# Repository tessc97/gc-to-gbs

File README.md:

# GCtoGBS
The GCtoGBS board is supposed to provide a cheaper way to connect (mainly Nintendo) consoles to a [gbs-control](https://github.com/ramapcsx2/gbs-control) by using cheap components and VGA/Aux cables.

It provides multiple solder jumpers and optional components to configure your signal output exactly to your needs for any console.

This probably makes the most sense if you have multiple consoles that you want to hook up to your gbs-control. Just order a bunch of PCBs from JLCPCB or any other PCB manufacturer, order the parts and assemble yourself. I designed the board to be able to be hand soldered.

This is my first PCB design project. Feel free to point out any mistakes or improvements I could make. This project is also completely open source.

PS: The original name of this project was gc-to-vga because I planned on doing one board per console. Then I changed it to gc-to-gbs because most modern VESA VGA monitors won't be able to read the RGBS/RGBHV signal this outputs. Last, I decided to make this board configurable by jumpers and optional components so it's one board for every console/mod but stuck with the name.

# Settings
Depending on the console or mod you have, you need to set jumpers and add/leave out components to match the following specs.

## Sync
### Native CSync
If your console outputs native CSync, you have the following options:
* Console outputs TTL CSync:
    * Solder jumper JP4 if you do not have a 100 Ohm resistor to ground on your GBS
    * Add a 470 Ohm resistor to R4 if you have the 100 Ohm resistor on your GBS
* Console outputs 75 Ohm CSync
    * Solder jumper JP4; 100 Ohm resistor to ground on GBS should be present

**Never solder JP4 on a PAL SNES or Gamecube as these have +12V on Pin 3**

### LM1881 Sync
If you want to use the built-in LM1881 for CSync and VSync, you need to first select the signal you want to strip Sync from:
* For Sync on Green solder JP1
* For Sync on Luma solder JP2
* For Sync on Composite solder JP3

Then you need to do one of the following:
* Solder jumper JP5 if you need a TTL signal (no 100 Ohm from Sync to GND on GBS)
* Add a 470 Ohm resistor to R5 if you need a 75 Ohm signal

If you want to add VSync to your VGA cable, do one of the following:
* Solder jumper JP6
* Add 470 Ohm resistor to R6

I'm not entirely sure yet which of these is better for the GBS, but since most people only solder a 100 Ohm resistor to ground on the pin that is connected to CSync/HSync, the GBS probably expects a TTL signal (if any at all), so it's probably best to just solder the jumper closed.

If you don't need VSync and your console has built in CSync, you can leave out the LM1881.

## RGB signal
### 75 Ohm termination
Some consoles are already 75 Ohm terminated (PAL Gamecube, NESRGB) but some need a 75 Ohm resistor to ground on each of the RGB color lines.

Solder a 75 Ohm resistor to R3, R7 and R8 if you console needs the 75 Ohm termination, i.e. the PAL SNES.

### Brightness
If you need to control the brigthness of your RGB signal, you can add three capacitors to C3, C4 and C5. According to [this](https://gamesx.com/wiki/doku.php?id=av:nintendomultiav), the PAL Gamecube needs a 220uF cap on every RGB line but the PAL SNES does not due to a different RGB circuit.

Some other documentations and threads also mention 470uF caps. I have not read into the whole thing but you might want to try different values here.

## Example settings
### PAL Gamecube (100R on GBS Sync to GND)
Soldered jumpers:
* JP3 for Sync on Composite
* JP6 for TTL level VSync (or no VSync at all)

Components:
* 470 Ohm resistor on R5
* 220uF capacitors on C4, C5 and C6

### NESRGB configured for TTL (no 100R on GBS Sync to GND)
Soldered jumpers:
* JP4 for TTL level CSync from MultiAV Pin 3
* JP7, JP8 and JP9 because NESRGB has built-in 220uF caps

### PAL SNES (100R on GBS Sync to GND)
Soldered jumpers:
* JP2 for Sync on Luma
* JP7, JP8 and JP9 to bypass the capacitors

Components:
* 470 Ohm resistor on R5
* 75 Ohm resistors on R3, R7 and R8 for 75 Ohm Termination

# Required components
These are "optional" if your console already has CSync and you don't need VSync.
* 100nF capacitors on C1, C2 and C3
* 75 Ohm resistor on R1
* 680k resistor on R2

# Connectors
I spec'd this for the following connectors:
* 12 pin JST-XH header
    * plus MultiAV to 12 pin JST connector
* D-Sub 15 HD female horizontal socket for VGA
* SJ1-3533NG horizontal 3.5mm audio jack socket

You can also just solder the conductors to the board. I will probably not bother with the 12-pin JST connector and header myself as those are kind of expensive.
I ordered some MutliAV plugs from Aliexpress to make a full-on adapter.

# Case
I am currently designing a 3D-printable case for this board. I will update the repository once I finished and tested it.

# ToDos
* Update Readme with images
* Design 3D-printable case
* Assemble prototye and test

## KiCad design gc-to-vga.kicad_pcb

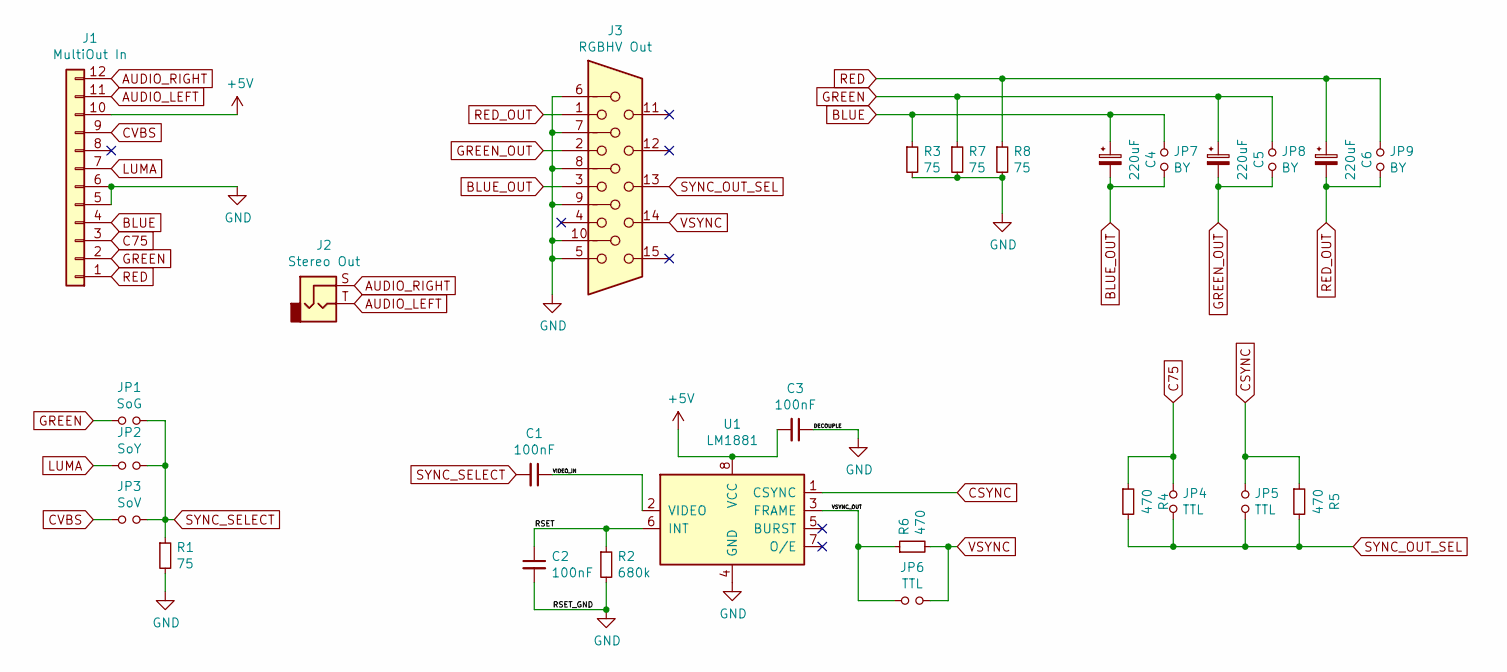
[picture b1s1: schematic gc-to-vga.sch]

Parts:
C1, C3: 100nF; C_0805_2012Metric; Part CL21B104KBCNFNC‎
C2: 100nF; C_0805_2012Metric
C4, C5, C6: 220uF; CP_Radial_D8.0mm_P3.80mm; Part UWX1A221MCL1GB‎
J1: MultiOut In; JST_XH_B12B-XH-A_1x12_P2.50mm_Vertical; Part B12B-XH-A
J2: Stereo Out; Jack_3.5mm_CUI_SJ1-3533NG_Horizontal; Part ‎SJ1-3533N‎
J3: RGBHV Out; DSUB-15-HD_Female_Horizontal_P2.29x1.98mm_EdgePinOffset3.03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; Part L717HDE15PD4CH4R‎
JP1: SoG; SolderJumper-2_P1.3mm_Open_TrianglePad1.0x1.5mm
JP2: SoY; SolderJumper-2_P1.3mm_Open_TrianglePad1.0x1.5mm
JP3: SoV; SolderJumper-2_P1.3mm_Open_TrianglePad1.0x1.5mm
JP4, JP5, JP6: TTL; SolderJumper-2_P1.3mm_Open_TrianglePad1.0x1.5mm
JP7, JP8, JP9: BY; SolderJumper-2_P1.3mm_Open_TrianglePad1.0x1.5mm
R1: 75; R_1206_3216Metric_Pad1.30x1.75mm_HandSolder; Part RK73H2BTTD75R0F‎
R2: 680k; R_1206_3216Metric_Pad1.30x1.75mm_HandSolder
R3, R7, R8: 75; R_1206_3216Metric_Pad1.30x1.75mm_HandSolder
R4, R5: 470; R_1206_3216Metric_Pad1.30x1.75mm_HandSolder; Part CRG1206F470R‎
R6: 470; R_1206_3216Metric_Pad1.30x1.75mm_HandSolder
U1: LM1881; SOIC-8_3.9x4.9mm_P1.27mm; Part ‎LM1881MX/NOPB‎

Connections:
+5V: C3.2, J1.10, U1.8 (VCC)
/RSET: C2.1, R2.1, U1.6 (INT)
/VIDEO_IN: C1.1, U1.2 (VIDEO)
/VSYNC_OUT: JP6.1, R6.1, U1.3 (FRAME)
AUDIO_LEFT: J1.11, J2.T
AUDIO_RIGHT: J1.12, J2.S
BLUE: C4.1, J1.4, JP7.1, R3.1
BLUE_OUT: C4.2, J3.3, JP7.2
C75: J1.3, JP4.1, R4.1
CSYNC: JP5.1, R5.1, U1.1 (CSYNC)
CVBS: J1.9, JP3.1
GND: C2.2, C3.1, J1.5, J1.6, J3.5, J3.6, J3.7, J3.8, J3.9, J3.10, R1.2, R2.2, R3.2, R7.2, R8.2, U1.4 (GND)
GREEN: C5.1, J1.2, JP1.1, JP8.1, R7.1
GREEN_OUT: C5.2, J3.2, JP8.2
LUMA: J1.7, JP2.1
RED: C6.1, J1.1, JP9.1, R8.1
RED_OUT: C6.2, J3.1, JP9.2
SYNC_OUT_SEL: J3.13, JP4.2, JP5.2, R4.2, R5.2
SYNC_SELECT: C1.2, JP1.2, JP2.2, JP3.2, R1.1
VSYNC: J3.14, JP6.2, R6.2

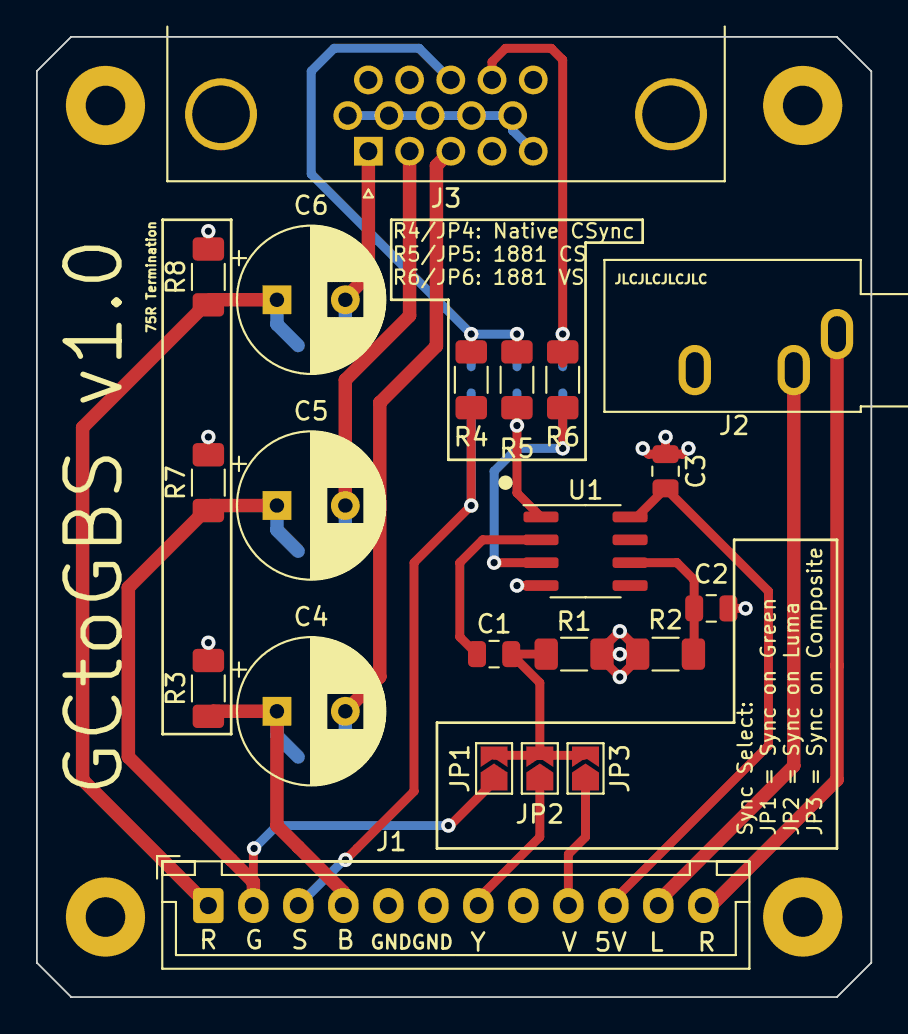
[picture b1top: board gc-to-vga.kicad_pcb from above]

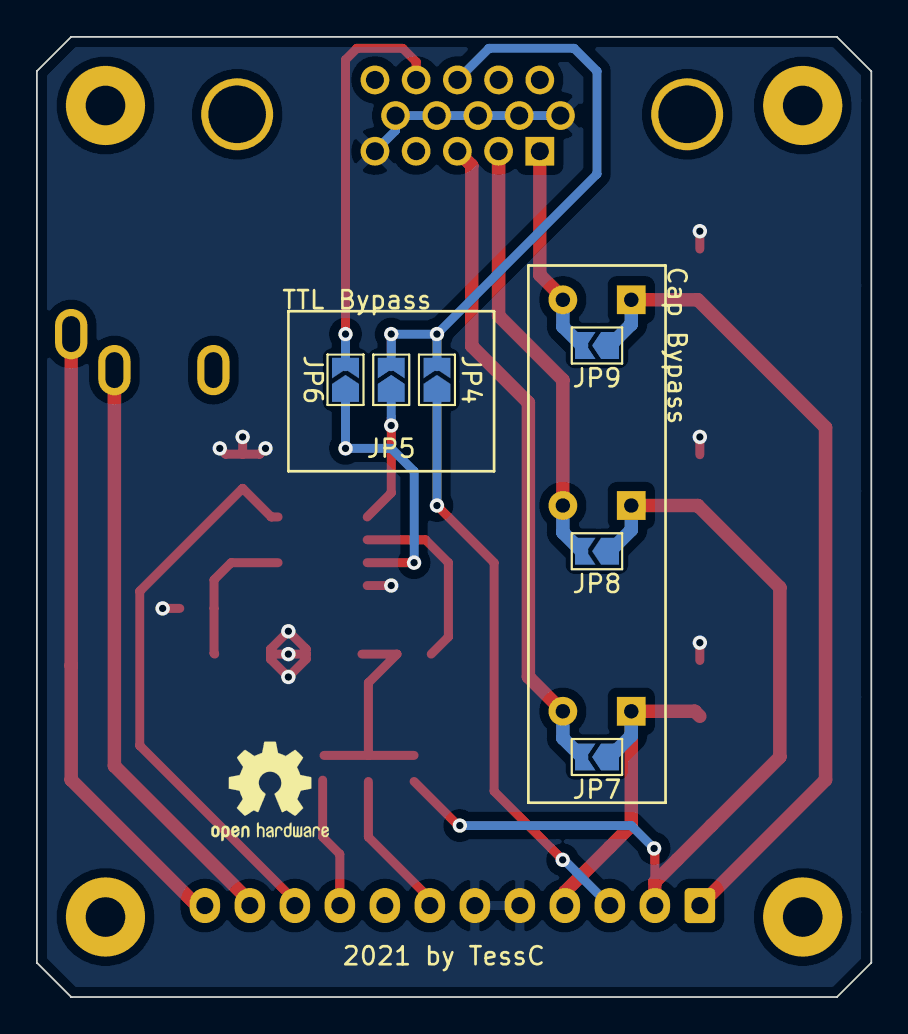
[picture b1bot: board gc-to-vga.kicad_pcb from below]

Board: 2 copper layers, 46.4 x 53.3 mm, 27 parts (6 on the bottom side), 20 nets.

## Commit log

2021-09-27 add kicad files
2021-09-27 fix errors in readme
